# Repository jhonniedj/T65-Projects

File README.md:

# T65 Projects
 
TODO:
- interrupt voor dtmf/sample detect
- dfplayer mini aansturen
- on-hook off-hook detectie met SLIC print
- belspanning genereren
- aardetoets uitlezen
- programma's samenvoegen

- In kicad(?) PCB ontwerpen

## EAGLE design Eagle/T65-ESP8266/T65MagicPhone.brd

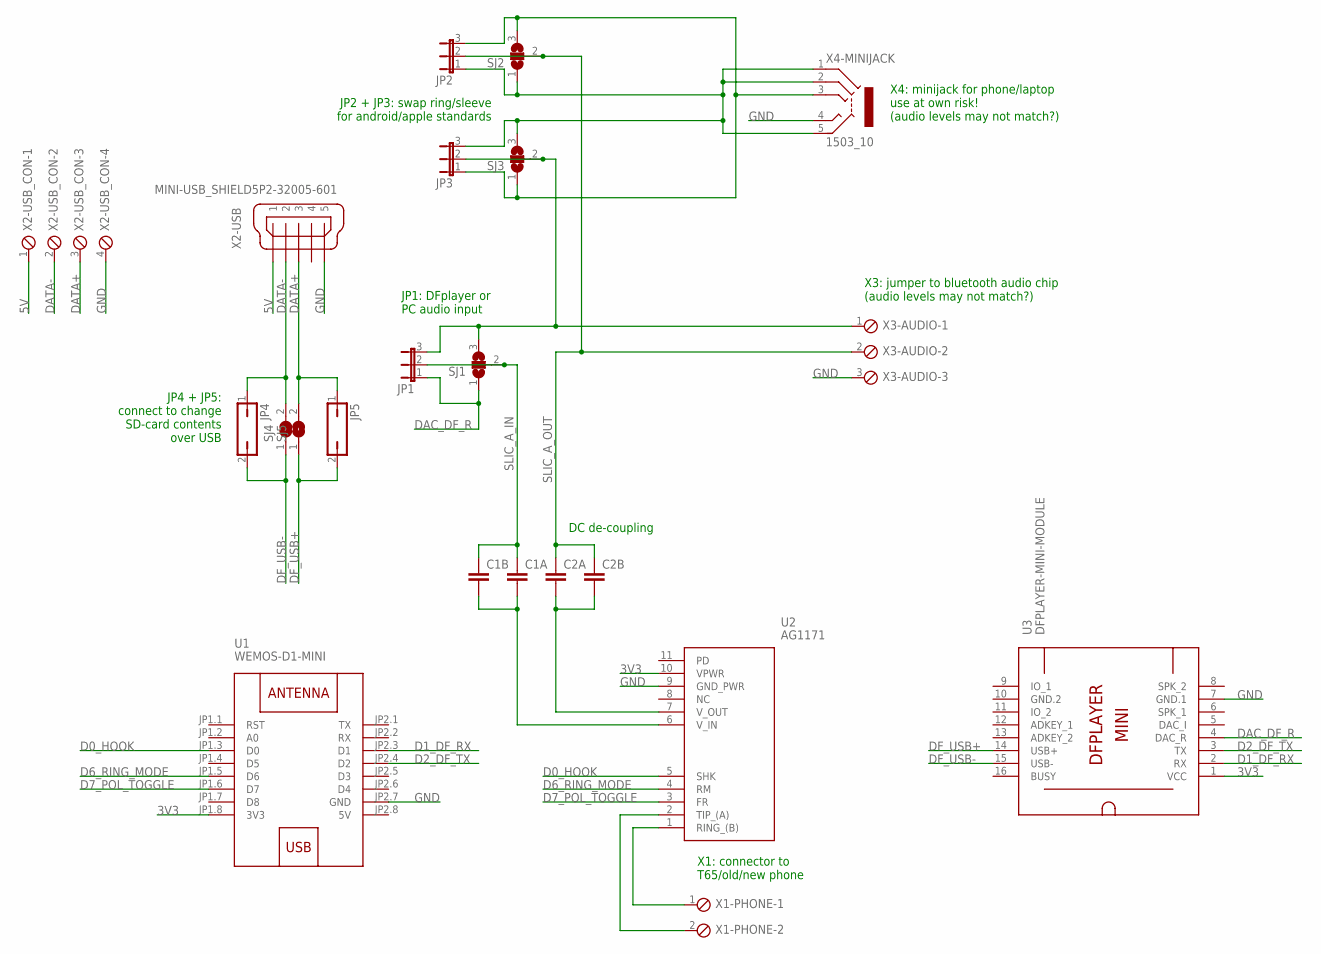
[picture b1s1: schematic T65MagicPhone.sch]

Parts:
C1A, C2A: C-EUC0805K; C0805K
C1B, C2B: C-EU025-030X050; C025-030X050
JP1, JP2, JP3: JP2E; JP2
JP4, JP5: JP1Q; JP1
SJ1, SJ2, SJ3: SJ2W; SJ_2
SJ4, SJ5: SJ
U1: WEMOS-D1-MINI
U2: AG1171
U3: DFPLAYER-MINI-MODULE
X1-PHONE: MPT2; 2POL254
X2-USB: MINI-USB_SHIELD5P2-32005-601; 32005-601
X2-USB_CON: MPT4; 4POL254
X3-AUDIO: MPT3; 3POL254
X4-MINIJACK: 1503_10

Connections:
3V3: U1.JP1.8 (3V3), U2.10 (VPWR), U3.1 (VCC)
5V: U1.JP2.8 (5V), X2-USB.1, X2-USB_CON.1
A_TIP: U2.2 (TIP_(A)), X1-PHONE.2
B_RING: U2.1 (RING_(B)), X1-PHONE.1
D0_HOOK: U1.JP1.3 (D0), U2.5 (SHK)
D1_DF_RX: U1.JP2.3 (D1), U3.2 (RX)
D2_DF_TX: U1.JP2.4 (D2), U3.3 (TX)
D6_RING_MODE: U1.JP1.5 (D6), U2.4 (RM)
D7_POL_TOGGLE: U1.JP1.6 (D7), U2.3 (FR)
DAC_DF_R: JP1.1, SJ1.1, U3.4 (DAC_R)
DATA+: JP5.1, SJ5.2, X2-USB.3, X2-USB_CON.3
DATA-: JP4.1, SJ4.2, X2-USB.2, X2-USB_CON.2
DF_USB+: JP5.2, SJ5.1, U3.14 (USB+)
DF_USB-: JP4.2, SJ4.1, U3.15 (USB-)
GND: U1.JP2.7 (GND), U2.9 (GND_PWR), U3.7 (GND.1), X2-USB.5, X2-USB_CON.4, X3-AUDIO.3, X4-MINIJACK.4
GND.2: U3.10 (GND.2)
unnamed: JP2.1, JP3.3, SJ2.1, SJ3.3, X4-MINIJACK.1, X4-MINIJACK.2, X4-MINIJACK.5
unnamed: JP2.3, JP3.1, SJ2.3, SJ3.1, X4-MINIJACK.3
unnamed: JP1.3, JP3.2, SJ1.3, SJ3.2, X3-AUDIO.1
SLIC_A_IN: C1A.1, C1B.1, JP1.2, SJ1.2
SLIC_A_OUT: C2A.1, C2B.1, JP2.2, SJ2.2, X3-AUDIO.2
V_IN: C1A.2, C1B.2, U2.6 (V_IN)
V_OUT: C2A.2, C2B.2, U2.7 (V_OUT)

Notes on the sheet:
JP4 + JP5: connect to change SD-card contents over USB
DC de-coupling
X4: minijack for phone/laptop use at own risk! (audio levels may not match?)
JP2 + JP3: swap ring/sleeve for android/apple standards
JP1: DFplayer or PC audio input
X3: jumper to bluetooth audio chip (audio levels may not match?)
X1: connector to T65/old/new phone

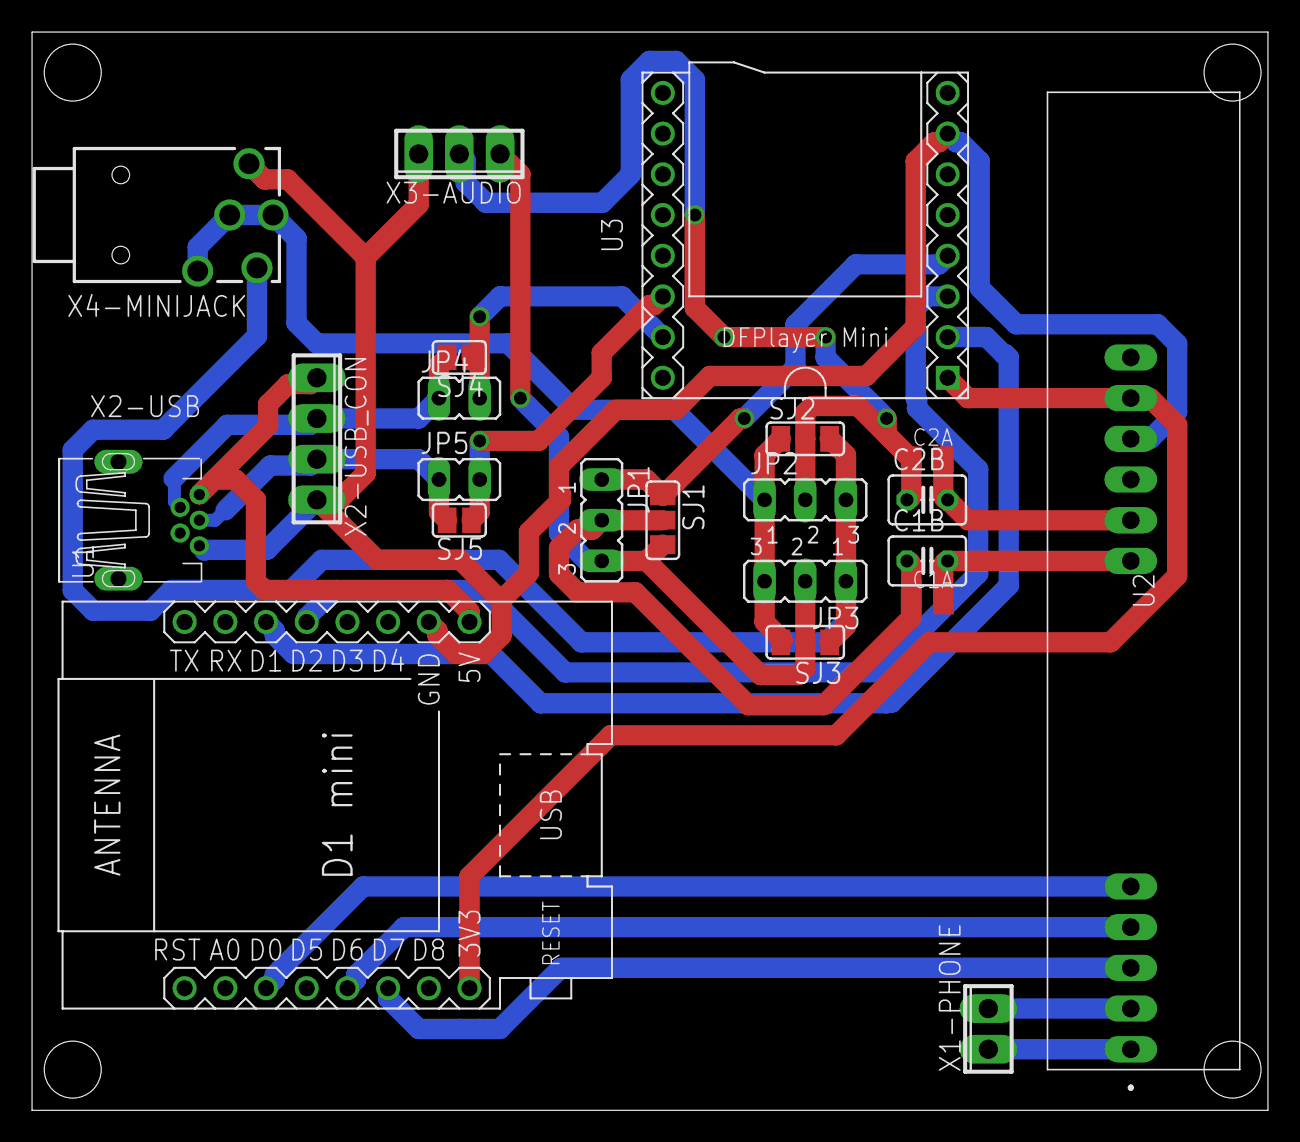
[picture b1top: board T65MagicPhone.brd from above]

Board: 2 copper layers, 77.1 x 67.3 mm, 22 parts (0 on the bottom side), 22 nets.

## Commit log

2020-11-07 added pulse
    - added pulse
    - refined dtmf detect to prevent holding buttons will repeat reading
    - added todo to README
2020-11-07 add serial screenshots
    - add screenshots from serial output
    - add oscilloscope image from A0 reading of SLIC module
    - cleanup serial port start texts
2020-11-08 hookdetect + ringOTA + DFplay
    - add hookdetect program
    - add DFPlay program
    - add OTA to ring program
    - add photo of prototype
2021-04-18 add schematics

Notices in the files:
parts and their libraries:
diy-modules: Released under the Creative Commons Attribution 4.0 International License: http://creativecommons.org/licenses/by/4.0
